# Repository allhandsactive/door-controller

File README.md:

# door-controller
Code + PCB for ESP-based RFID card access door control

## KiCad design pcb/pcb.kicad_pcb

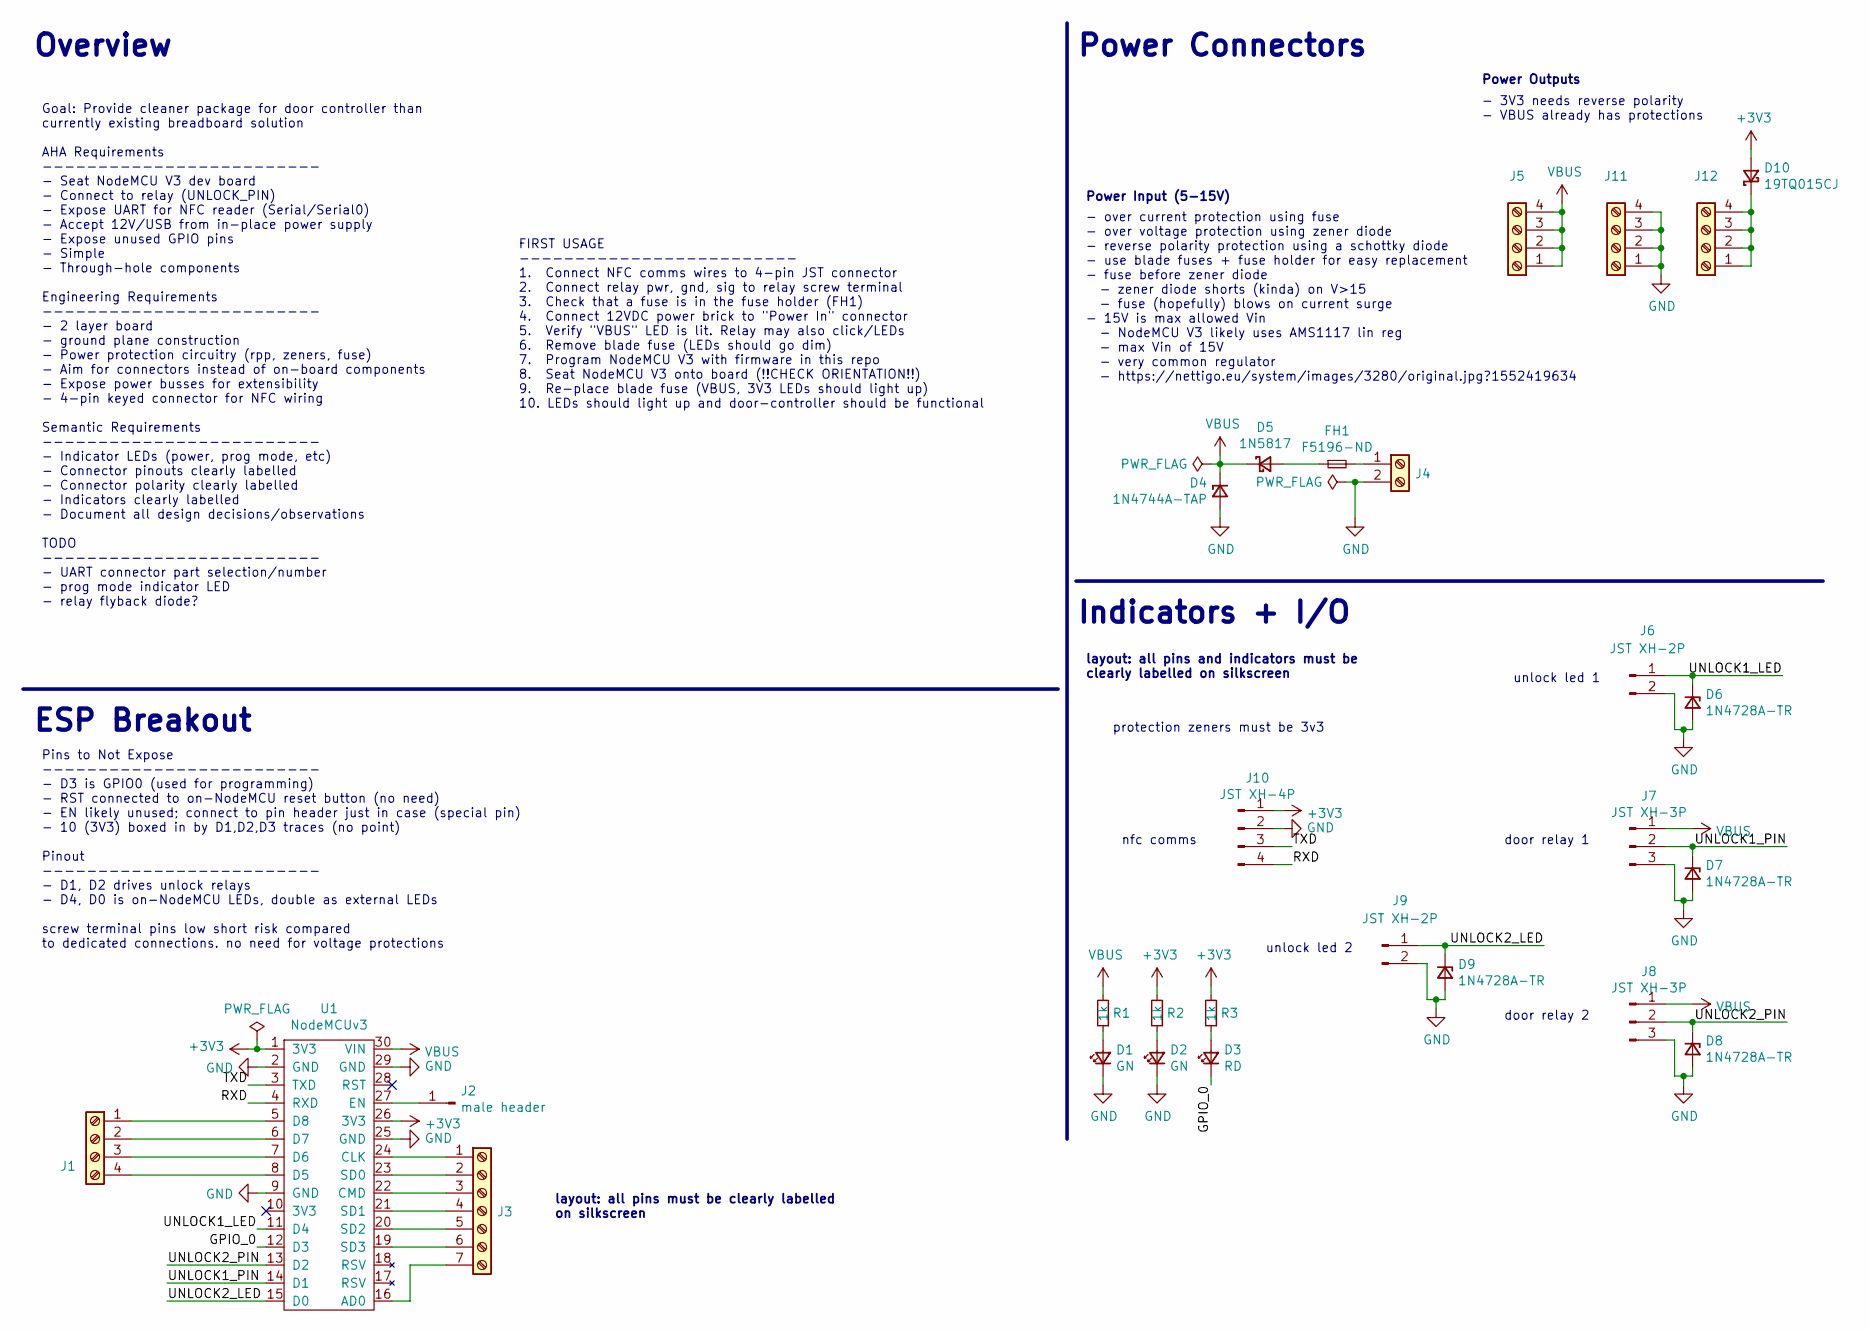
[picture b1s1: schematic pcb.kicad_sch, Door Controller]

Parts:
D1, D2: GN; LED_D5.0mm; PartNo LTL-4233; Digi-Key 160-1130-ND
D3: RD; LED_D5.0mm; PartNo LTL-4263; Digi-Key 160-1964-ND
D4: 1N4744A-TAP; D_DO-41_SOD81_P10.16mm_Horizontal; PartNo 1N4744A-TAP; Digi-Key 1N4744A-TAPGICT-ND
D5: 1N5817; D_DO-41_SOD81_P10.16mm_Horizontal; PartNo 1N5817-E3/54; Digi-Key 1N5817-E3/54GICT-ND
D6, D7, D8, D9: 1N4728A-TR; D_DO-41_SOD81_P10.16mm_Horizontal; PartNo 1N4728A-TR; Digi-Key 1N4728AVSCT-ND
D10: 19TQ015CJ; TO-220-2_Vertical; PartNo 19TQ015CJ; Digi-Key 1655-1005-ND
FH1: F5196-ND; Blade Fuse Holder; PartNo 178.6164.0002; Digi-Key F5196-ND
J1: Screw_Terminal_01x06; TerminalBlock_Phoenix_MPT-0,5-4-2.54_1x04_P2.54mm_Horizontal; PartNo 1725672; Digi-Key 277-1275-ND
J2: male header; PinHeader_1x01_P2.54mm_Vertical; PartNo 951101-8622-AR; Digi-Key 3M156413-01-ND
J3: Screw_Terminal_01x07; TerminalBlock_Phoenix_MPT-0,5-7-2.54_1x07_P2.54mm_Horizontal; PartNo 1725708; Digi-Key 277-1278-ND
J4: Screw_Terminal_01x02; TerminalBlock_Phoenix_MPT-0,5-2-2.54_1x02_P2.54mm_Horizontal; PartNo 1725656; Digi-Key 277-1273-ND
J5, J11, J12: Screw_Terminal_01x04; TerminalBlock_Phoenix_MPT-0,5-4-2.54_1x04_P2.54mm_Horizontal; PartNo 1725672; Digi-Key 277-1275-ND
J6, J9: JST XH-2P; JST_XH_B2B-XH-AM_1x02_P2.50mm_Vertical; PartNo B2B-XH-A-GU; Digi-Key 455-2946-ND
J7, J8: JST XH-3P; JST_XH_B3B-XH-AM_1x03_P2.50mm_Vertical; PartNo B3B-XH-AM(LF)(SN); Digi-Key 455-2231-ND
J10: JST XH-4P; JST_XH_B4B-XH-AM_1x04_P2.50mm_Vertical; PartNo B4B-XH-AM(LF)(SN); Digi-Key 455-2237-ND
R1, R2, R3: 1k; R_Axial_DIN0207_L6.3mm_D2.5mm_P10.16mm_Horizontal; PartNo CF14JT1K00; Digi-Key CF14JT1K00CT-ND
U1: NodeMCUv3

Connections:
+3V3: D10.2 (A), J10.1, R2.2, R3.2, U1.1 (3V3), U1.26 (3V3)
/GPIO_0: D3.1 (K), U1.12 (D3)
/RXD: J10.4, U1.4 (RXD)
/TXD: J10.3, U1.3 (TXD)
/UNLOCK1_LED: D6.1 (K), J6.1, U1.11 (D4)
/UNLOCK1_PIN: D7.1 (K), J7.2, U1.14 (D1)
/UNLOCK2_LED: D9.1 (K), J9.1, U1.15 (D0)
/UNLOCK2_PIN: D8.1 (K), J8.2, U1.13 (D2)
GND: D1.1 (K), D2.1 (K), D4.2 (A), D6.2 (A), D7.2 (A), D8.2 (A), D9.2 (A), J4.2, J6.2, J7.3, J8.3, J9.2, J10.2, J11.1, J11.2, J11.3, J11.4, U1.2 (GND), U1.9 (GND), U1.25 (GND), U1.29 (GND)
unnamed: D1.2 (A), R1.1
unnamed: D2.2 (A), R2.1
unnamed: D3.2 (A), R3.1
unnamed: D5.2 (A), FH1.1
unnamed: D10.1 (K), J12.1, J12.2, J12.3, J12.4
unnamed: FH1.2, J4.1
unnamed: J1.1, U1.5 (D8)
unnamed: J1.2, U1.6 (D7)
unnamed: J1.3, U1.7 (D6)
unnamed: J1.4, U1.8 (D5)
unnamed: J2.1, U1.27 (EN)
unnamed: J3.1, U1.24 (CLK)
unnamed: J3.2, U1.23 (SD0)
unnamed: J3.3, U1.22 (CMD)
unnamed: J3.4, U1.21 (SD1)
unnamed: J3.5, U1.20 (SD2)
unnamed: J3.6, U1.19 (SD3)
unnamed: J3.7, U1.16 (AD0)
VBUS: D4.1 (K), D5.1 (K), J5.1, J5.2, J5.3, J5.4, J7.1, J8.1, R1.2, U1.30 (VIN)

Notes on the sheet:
Power Outputs
Overview
Indicators + I/O
door relay 2
- 3V3 needs reverse polarity - VBUS already has protections
Power Connectors
layout: all pins must be clearly labelled on silkscreen
ESP Breakout
protection zeners must be 3v3
- over current protection using fuse - over voltage protection using zener diode - reverse polarity protection using a schottky diode - use blade fuses + fuse holder for easy replacement - fuse before zener diode - zener diode shorts (kinda) on V>15 - fuse (hopefully) blows on current surge - 15V i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
unlock led 2
unlock led 1
layout: all pins and indicators must be clearly labelled on silkscreen
Goal: Provide cleaner package for door controller than currently existing breadboard solution AHA Requirements ------------------------- - Seat NodeMCU V3 dev board - Connect to relay (UNLOCK_PIN) - Expose UART for NFC reader (Serial/Serial0) - Accept 12V/USB from in-place power supply - Expose unu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
door relay 1
Power Input (5-15V)
FIRST USAGE ------------------------- 1. Connect NFC comms wires to 4-pin JST connector 2. Connect relay pwr, gnd, sig to relay screw terminal 3. Check that a fuse is in the fuse holder (FH1) 4. Connect 12VDC power brick to "Power In" connector 5. Verify "VBUS" LED is lit. Relay may also click/LEDs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
nfc comms
Pins to Not Expose ------------------------- - D3 is GPIO0 (used for programming) - RST connected to on-NodeMCU reset button (no need) - EN likely unused; connect to pin header just in case (special pin) - 10 (3V3) boxed in by D1,D2,D3 traces (no point) Pinout ------------------------- - D1, D2 dri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

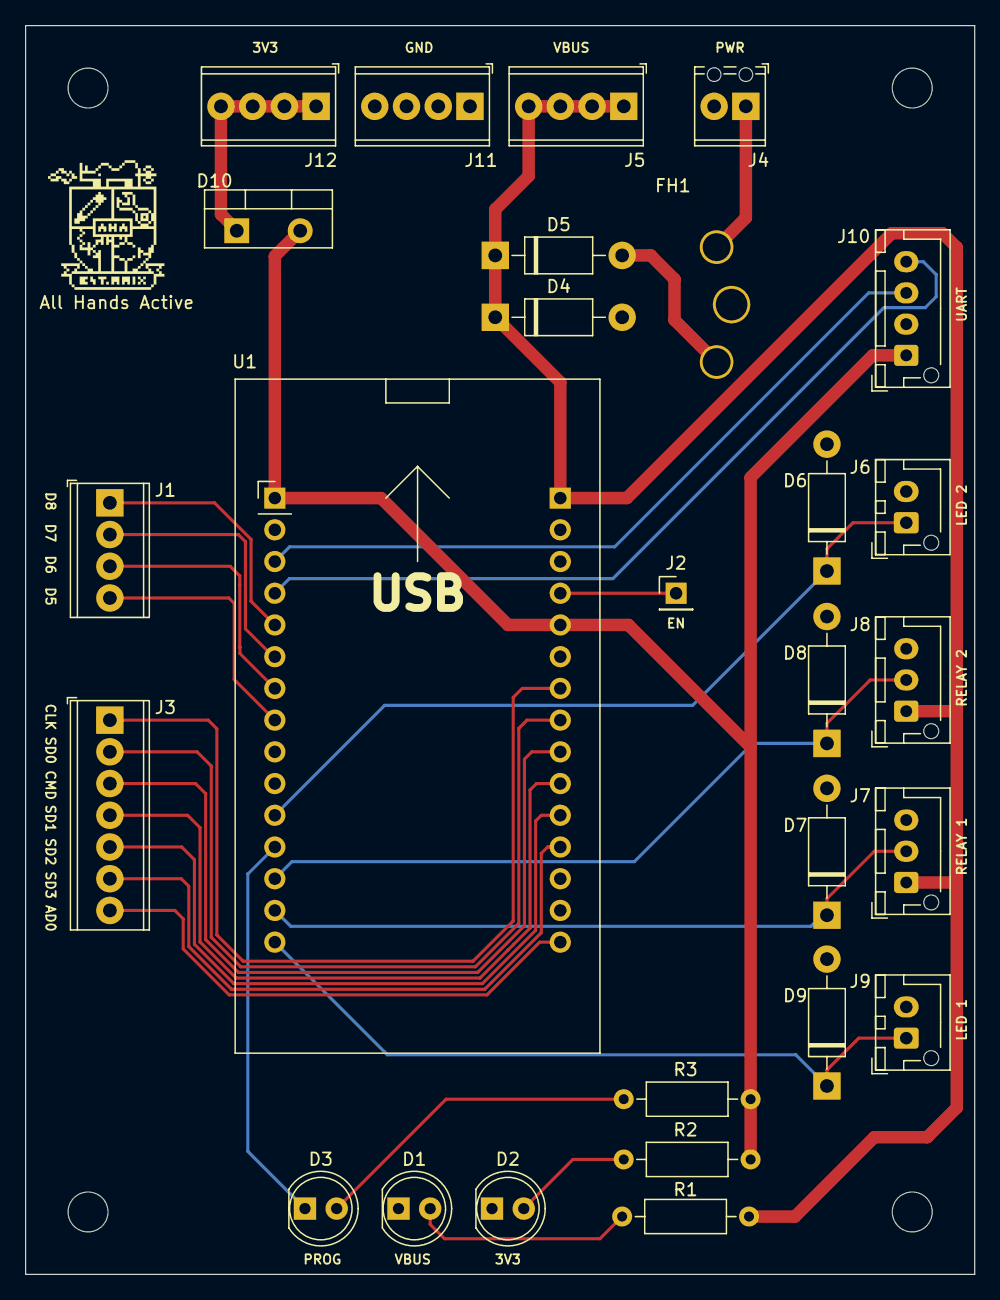
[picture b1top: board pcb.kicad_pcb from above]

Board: 2 copper layers, 76.0 x 100.0 mm, 31 parts (0 on the bottom side), 28 nets.

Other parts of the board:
H1, H2, H3, H4: MountingHole_3.2mm_M3

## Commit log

2020-07-26 Updated door access code to reflect newer OS (Raspberry Pi OS) and NFC Python lib (nfcpy). Cleaned up a few other code things as well.
2022-04-16 initial ESP daughter board work - pinout + sym + fp
2022-05-01 pcb pinout + protections
2022-05-01 added esp board datasheet to sch symbol
2022-05-01 updated esp board symbol name to its common name
2022-05-01 major schematic reorg+documentation
2022-05-01 gitignore PDFs
2022-05-03 UNLOCK_PIN change and connector selection for relay
2022-05-07 1n4148->1n4004 and connector changes
2022-05-07 schematic pinout edits + documentation
2022-05-07 ERC fixes - pwr_flags + nodemcuv3 power pins
2022-05-07 all-but-zener footprint assignment
2022-05-07 zener selection + footprint assignment
2022-05-07 footprint rename: lolinv3->NodeMCUv3
2022-07-29 Update to Kicad 6
2022-07-31 Update schematic with part numbers for BOM
2022-07-31 Layout components on PCB Board
2022-07-31 Route door controller pcb
2022-08-01 Added second relay and LED connectors to the PCB to allow controlling of two doors
